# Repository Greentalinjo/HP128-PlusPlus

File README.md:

# HP 128 Laser Wired Mouse Reverse Engineering 🖱️🔍

> **Disclaimer:** This project is strictly for **educational purposes**. The HP 128 laser mouse and its original design are the intellectual property of HP. This repository serves as a study in hardware reverse engineering, component analysis, and PCB layout techniques.

## What this is
This project is a complete, bottom-up reverse engineering of the HP 128 laser wired mouse. The goal of this research was to create a near-perfect, 1:1 functional clone of the original PCB. Every trace, jumper, component footprint, and silkscreen marking has been meticulously recreated to match the original factory board.

### Side-By-Side

#### Back:

#### Front:

## Teardown

<table>
  <thead>
    <tr>
      <th align="center" width="50%">1</th>
      <th align="center" width="50%">2</th>
    </tr>
  </thead>
  <tbody>
    <tr>
      <td align="center" valign="middle">
        
      </td>
      <td align="center" valign="middle">
        
      </td>
    </tr>
    <tr>
      <td valign="top">
        <h3 align="center">Initial inspection</h3>
        <p>The writing on the mouse is documenting identifying details, including the model number "TPA-P002M," a specific serial number, and the manufacturing date of "February 2024". The mouse is in its initial, fully assembled state.</p>
      </td>
      <td valign="top">
        <h3 align="center">Bottom Screw Access and Disassembly</h3>
        <p>Remove the sticker to reveal the primary bottom screw. Unscrew the screw and take the unit apart.</p>
      </td>
    </tr>
    <tr>
      <th align="center">3</th>
      <th align="center">4</th>
    </tr>
    <tr>
      <td align="center" valign="middle">
        
      </td>
      <td align="center" valign="middle">
        
      </td>
    </tr>
    <tr>
      <td valign="top">
        <h3 align="center">PCB top side</h3>
        <p>After removing the screw and separating the top and bottom shells, the top of the pcb is revealed. The visible parts are the microswitches, the scroll wheel and its rotary encoder, the scroll wheel button, the USB connector, and the laser sensor.</p>
      </td>
      <td valign="top">
        <h3 align="center">PCB bottom side</h3>
        <p>Flipping the board its finally possible to see the entire circuit. Including but not limited to the MCU, LDO, underside of the laser sensor, etc.</p>
      </td>
    </tr>
  </tbody>
</table>

## Component Analysis

The two most interesting components are obviously the MCU and the laser sensor.

### MCU - SN32F264X (SSOP28)

This MCU is a 32-Bit Cortex-M0 Micro-Controller manufactured by Sonix:

https://www.sonix.com.tw/article-en-998-24755

Whilst the datasheet is available and can be downloaded from the linked web page, a symbol for KiCad was not. So I had to create my own symbol for it.

### Laser sensor - PMW3610DM-SUDU

This is a laser sensor with a janky footprint that luckily was already created by two github users:

https://github.com/Good-Great-Grand-Wonderful/pmw3610dm-sudu

https://github.com/siderakb/pmw3610-pcb

Its datasheet is also readily available here:

https://www.epsglobal.com/Media-Library/EPSGlobal/Products/files/pixart/PMW3610DM-SUDU.pdf?ext=.pdf

## Schematic Extraction
A few hours, a digital multimeter in continuity mode, and some close-up images later a schematic was successfully extracted:

Some component values were not measured due to the need to de-solder them, and at the time of me working on this project I could not find the time to do so. These missing values are left as an exercise for the reader as is commonly said.

## 1:1 PCB Recreation

To recreate the PCB, A close-up image was adjusted to the correct scale and proportions using a website called Photopea:

Then, the image was placed in the PCB view in KiCad, and all of the components and traces were placed according to the image.

The most attention demanding part were the little things - The silkscreen writings, font sizes, component outlines, etc.

## What's next?
If you want to fabricate your own board or study the layout feel free to do so. 

Once I assemble this board there are a few interesting research directions I would like to go down with the Sonix MCU, and perhaps integrate wireless connectivity for the mouse as well.

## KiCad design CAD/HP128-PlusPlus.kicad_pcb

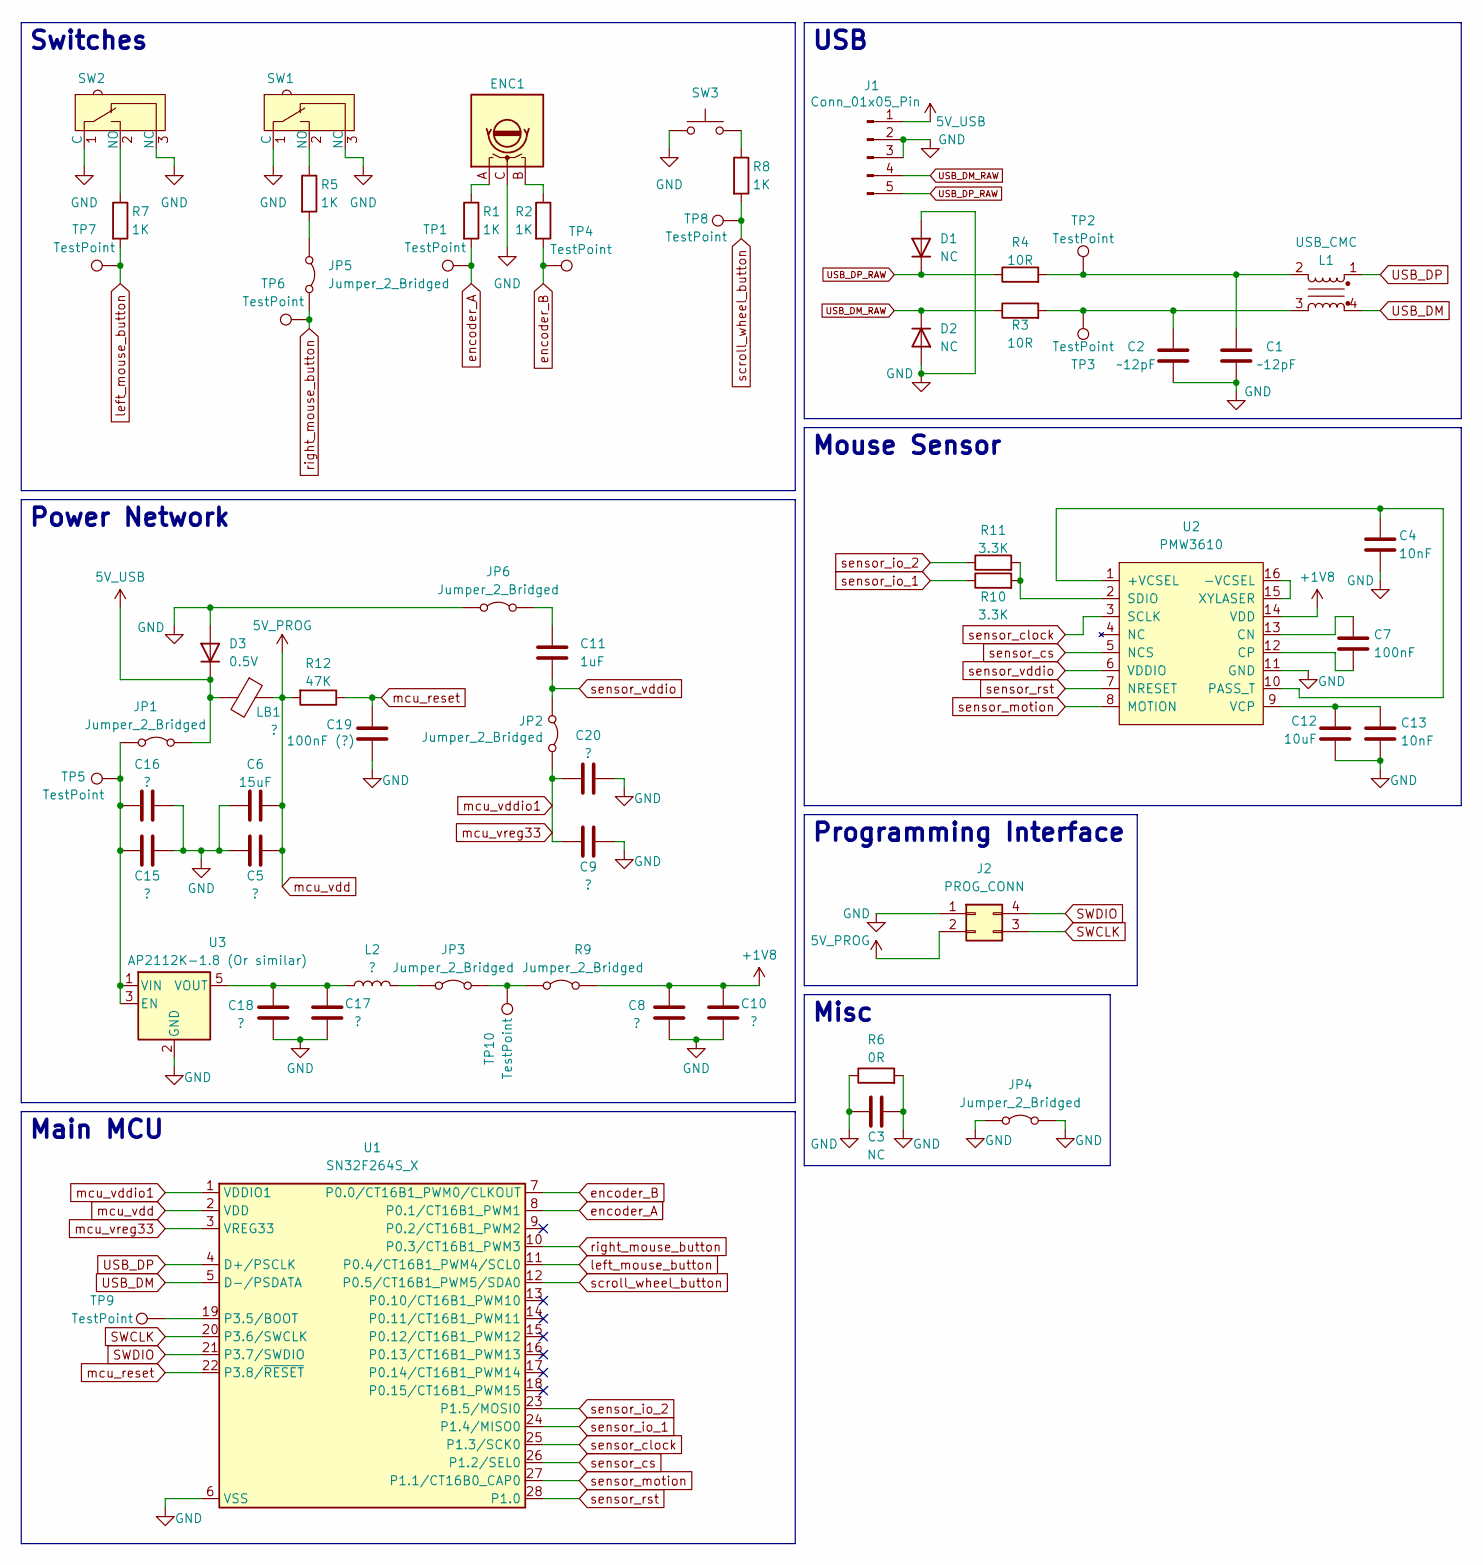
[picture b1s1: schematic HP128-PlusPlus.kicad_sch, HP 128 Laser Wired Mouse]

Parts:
C1, C2: ~12pF; C_0402_1005Metric
C3: NC; C_0603_1608Metric
C4, C13: 10nF; C_0402_1005Metric
C5, C8, C9, C16, C18, C20: ?; C_0402_1005Metric
C6: 15uF; C_0603_1608Metric
C7: 100nF; C_0402_1005Metric
C10, C15, C17: ?; C_0603_1608Metric
C11: 1uF; C_0402_1005Metric
C12: 10uF; C_0603_1608Metric
C19: 100nF (?); C_0402_1005Metric
D1, D2: NC; D_SOD-523
D3: 0.5V; D_SOD-523
ENC1: RotaryEncoder; RotaryEncoder_TTC_Staggered
J1: Conn_01x05_Pin; JST_PH_B5B-PH-K_1x05_P2.00mm_Vertical
J2: PROG_CONN; PinHeader_2x02_P1.75mm
JP1, JP2, JP3, JP4, JP5, JP6: Jumper_2_Bridged; R_1206_3216Metric
L1: USB_CMC; L_CommonModeChoke_Coilcraft_0805USB
L2: ?; L_0603_1608Metric
LB1: ?; L_0603_1608Metric
R1, R2, R5, R7, R8: 1K; R_0402_1005Metric
R3, R4: 10R; R_0402_1005Metric
R6: 0R; R_0603_1608Metric
R9: Jumper_2_Bridged; R_1206_3216Metric
R10, R11: 3.3K; R_0402_1005Metric
R12: 47K; R_0402_1005Metric
SW1, SW2: SW_SPDT; SW_Micro_Switch
SW3: SW_Push; SW_Tactile_6x6mm_2Pin
TP1, TP2, TP3, TP4, TP5, TP6, TP7, TP8, TP9, TP10: TestPoint; TestPoint_Pad_D1.5mm
U1: SN32F264S_X; SSOP-28_5.3x10.2mm_P0.65mm
U2: PMW3610; PMW3610DM-SUDU 16Pin
U3: AP2112K-1.8 (Or similar); SOT-23-5

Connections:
5V_USB: D3.1 (K), J1.1, JP1.2 (B), LB1.2
+1V8: C8.2, C10.2, R9.2 (B), U2.14 (VDD)
GND: C1.2, C2.2, C3.1, C3.2, C4.2, C5.1, C6.1, C8.1, C9.1, C10.1, C12.2, C13.2, C15.2, C16.2, C17.1, C18.1, C19.1, C20.2, D1.2 (A), D2.2 (A), D3.2 (A), ENC1.C, ENC1.MH1, ENC1.MH2, J1.2, J1.3, J2.1, JP4.1 (A), JP4.2 (B), JP6.1 (A), R6.1, R6.2, SW1.1 (C), SW1.3 (NC), SW2.1 (C), SW2.3 (NC), SW3.1, U1.6 (VSS), U2.11 (GND), U3.2 (GND)
unnamed: C1.1, L1.2, R4.2, TP2.1
unnamed: C2.1, L1.3, R3.2, TP3.1
unnamed: C15.1, C16.1, JP1.1 (A), TP5.1, U3.1 (VIN), U3.3 (EN)
unnamed: JP3.1 (A), L2.2
unnamed: JP3.2 (B), R9.1 (A), TP10.1
unnamed: JP5.1 (A), R5.2
unnamed: C11.1, JP6.2 (B)
unnamed: ENC1.A, R1.1
unnamed: ENC1.B, R2.1
unnamed: R8.1, SW3.2
unnamed: TP9.1, U1.19 (P3.5/BOOT)
unnamed: C4.1, U2.1 (+VCSEL), U2.10 (PASS_T)
unnamed: U2.15 (XYLASER), U2.16 (-VCSEL)
unnamed: C7.1, U2.13 (CN)
unnamed: C7.2, U2.12 (CP)
unnamed: R10.2, R11.2, U2.2 (SDIO)
unnamed: C12.1, C13.1, U2.9 (VCP)
unnamed: C17.2, C18.2, L2.1, U3.5 (VOUT)
unnamed: R7.1, SW2.2 (NO)
unnamed: R5.1, SW1.2 (NO)
SWCLK: J2.3, U1.20 (P3.6/SWCLK)
SWDIO: J2.4, U1.21 (P3.7/SWDIO)
USB_DM: L1.4, U1.5 (D-/PSDATA)
USB_DM_RAW: D2.1 (K), J1.4, R3.1
USB_DP: L1.1, U1.4 (D+/PSCLK)
USB_DP_RAW: D1.1 (K), J1.5, R4.1
encoder_A: R1.2, TP1.1, U1.8 (P0.1/CT16B1_PWM1)
encoder_B: R2.2, TP4.1, U1.7 (P0.0/CT16B1_PWM0/CLKOUT)
left_mouse_button: R7.2, TP7.1, U1.11 (P0.4/CT16B1_PWM4/SCL0)
mcu_reset: C19.2, R12.1, U1.22 (P3.8/~RESET)
mcu_vdd: C5.2, C6.2, J2.2, LB1.1, R12.2, U1.2 (VDD)
mcu_vddio1: C9.2, C20.1, JP2.2 (B), U1.1 (VDDIO1), U1.3 (VREG33)
right_mouse_button: JP5.2 (B), TP6.1, U1.10 (P0.3/CT16B1_PWM3)
scroll_wheel_button: R8.2, TP8.1, U1.12 (P0.5/CT16B1_PWM5/SDA0)
sensor_clock: U1.25 (P1.3/SCK0), U2.3 (SCLK)
sensor_cs: U1.26 (P1.2/SEL0), U2.5 (NCS)
sensor_io_1: R10.1, U1.24 (P1.4/MISO0)
sensor_io_2: R11.1, U1.23 (P1.5/MOSI0)
sensor_motion: U1.27 (P1.1/CT16B0_CAP0), U2.8 (MOTION)
sensor_rst: U1.28 (P1.0), U2.7 (NRESET)
sensor_vddio: C11.2, JP2.1 (A), U2.6 (VDDIO)

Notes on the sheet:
Mouse Sensor
USB
Programming Interface
Power Network
Misc
Switches
Main MCU

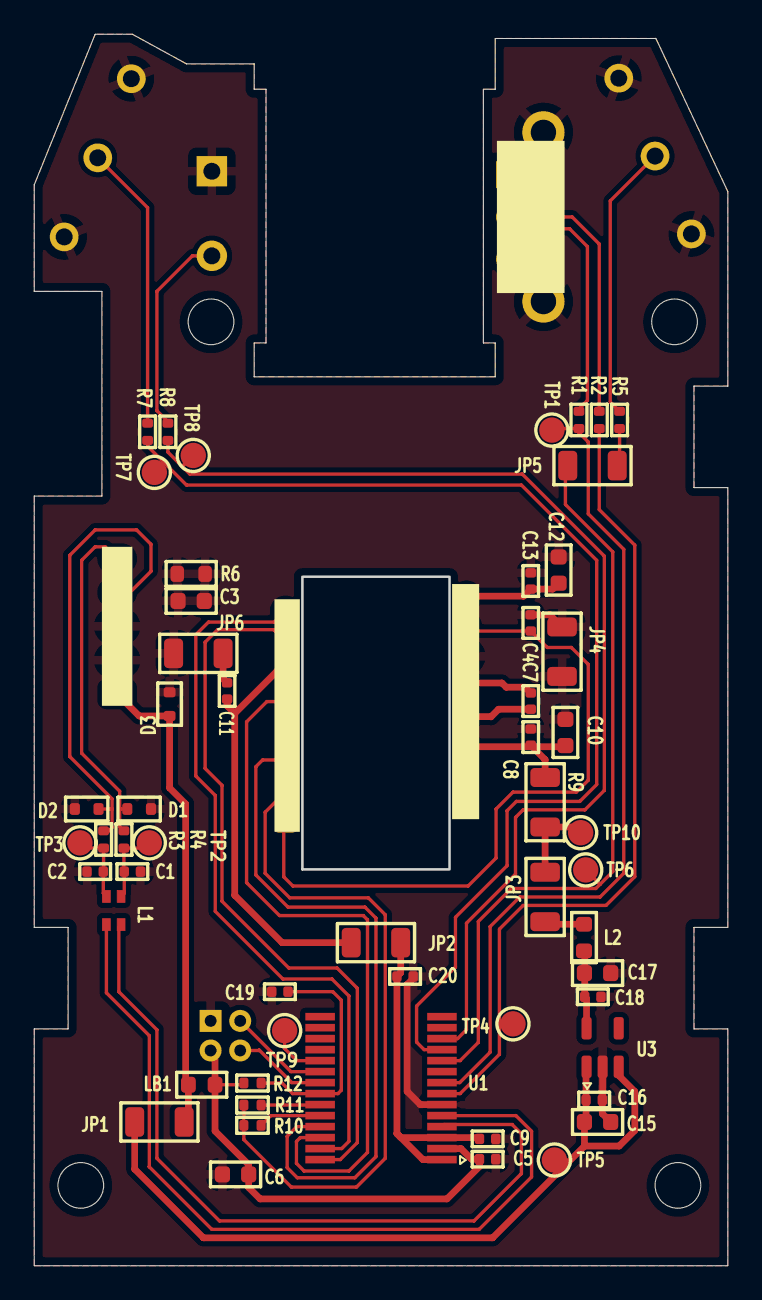
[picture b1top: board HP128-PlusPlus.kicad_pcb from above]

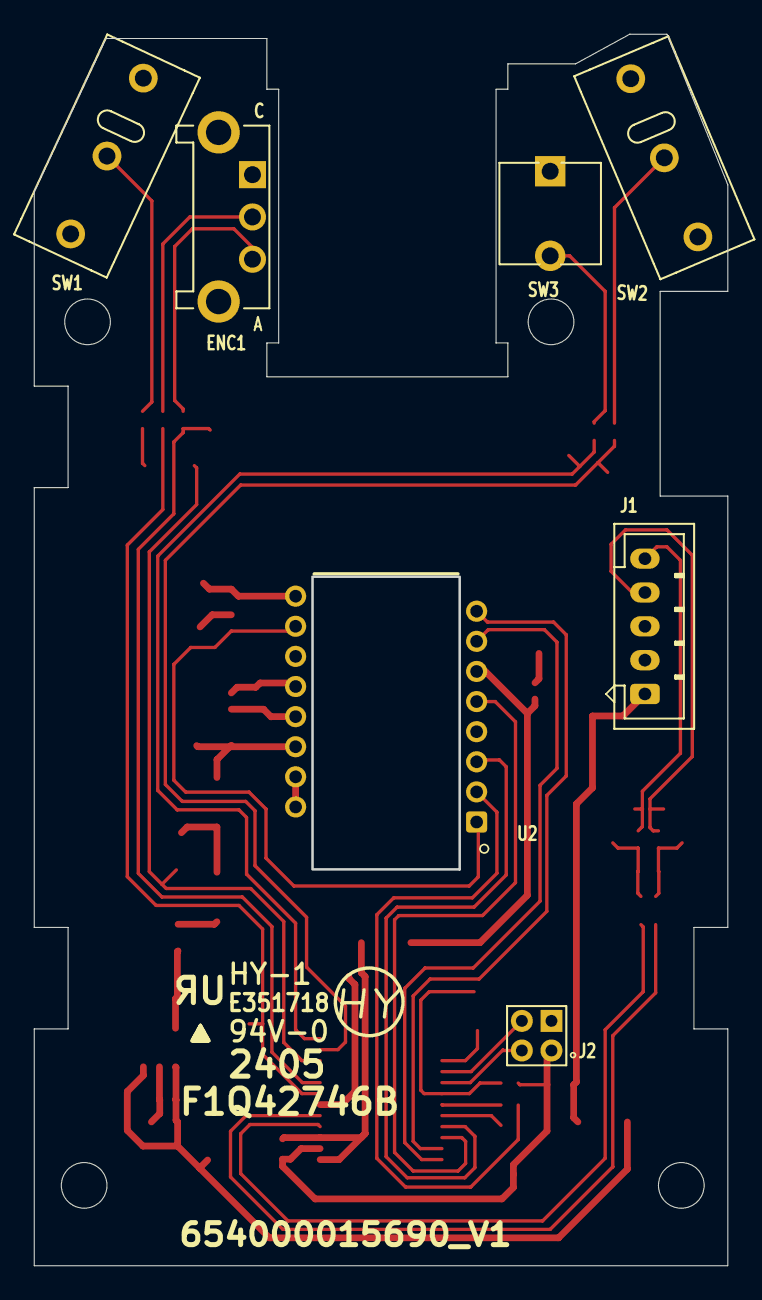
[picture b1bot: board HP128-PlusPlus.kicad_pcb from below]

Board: 2 copper layers, 40.9 x 72.7 mm, 62 parts (7 on the bottom side), 44 nets.

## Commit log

2026-03-08 Initial
2026-03-08 schem_img
2026-03-08 typos
2026-03-08 images
2026-03-08 table
2026-03-08 table2
2026-03-08 table3
